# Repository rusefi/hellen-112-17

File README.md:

# hellen-112-17

[User Documentation](https://github.com/rusefi/rusefi/wiki/Hellen112-17)

[Interactive Pinout](https://rusefi.com/docs/pinouts/hellen/hellen-112-17/)

[Firmware Source Code](https://github.com/rusefi/rusefi/tree/master/firmware/config/boards/hellen/hellen-112-17)

# Compatibility

Bosch 21126-1411020-45

Bosch 21126-1411020-49

Bosch 21126-1411020-70

Suzuki 33910-69L01

Polaris Slingshot 4015316

Maybe 391F2-03FA0 HYUNDAI I20 1.2 16V?

Maybe 39124-2B500 KIA FORTE 1.6?

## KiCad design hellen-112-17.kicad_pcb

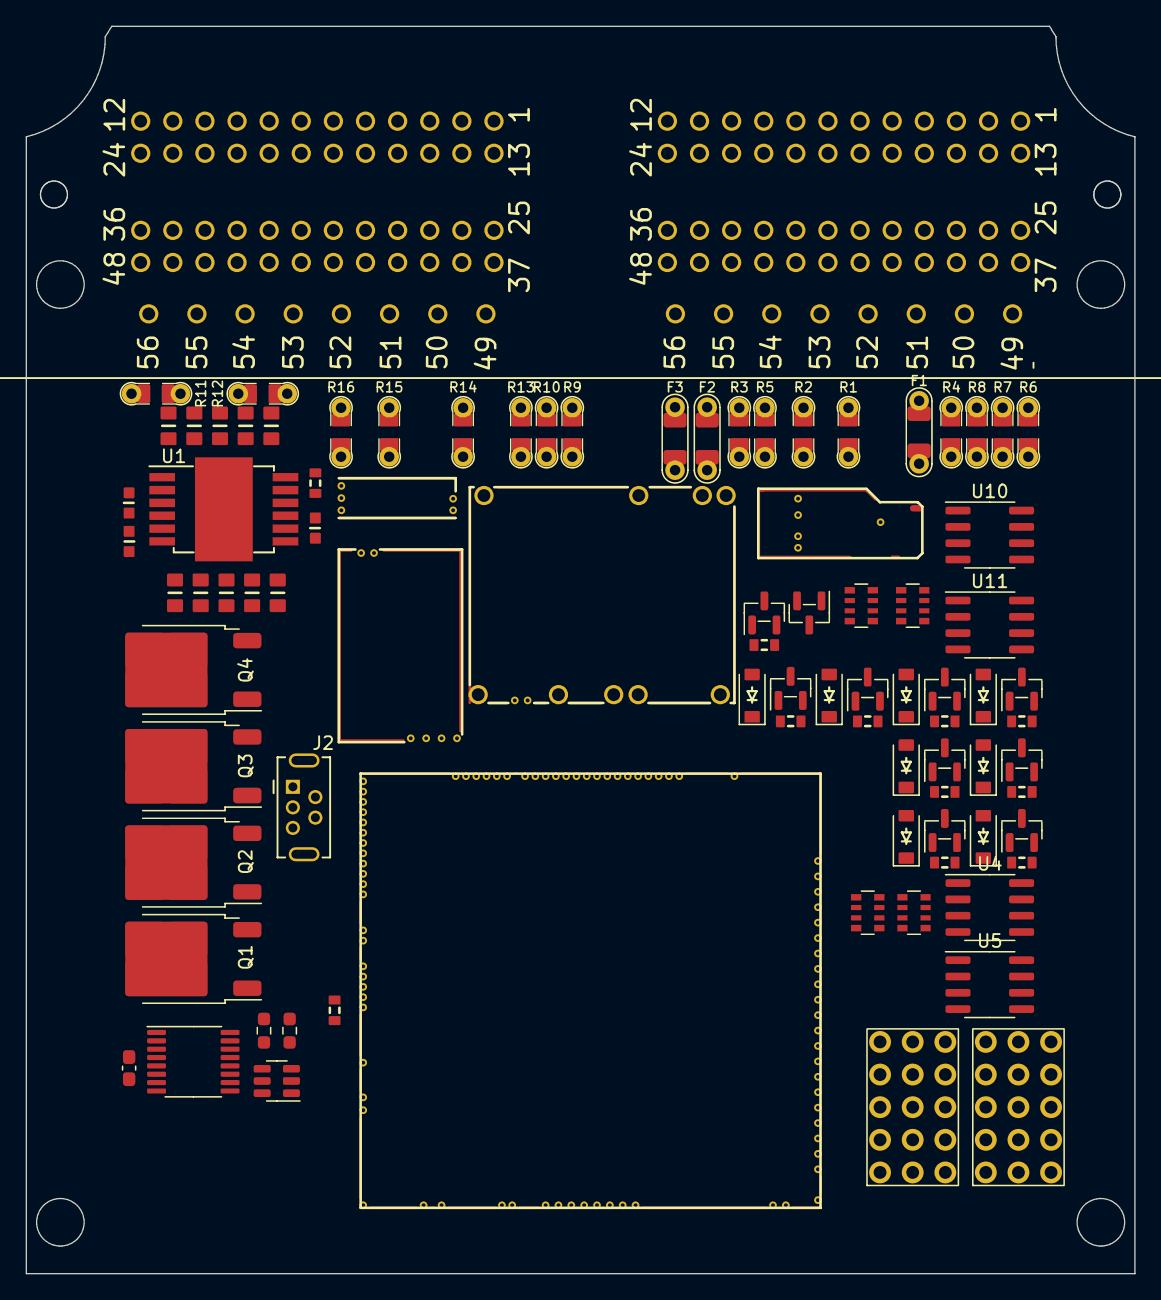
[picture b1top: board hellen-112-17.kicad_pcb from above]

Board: 2 copper layers, 86.3 x 97.1 mm, 88 parts (0 on the bottom side), 132 nets, no tracks yet.

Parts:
C1, C2, C3, C4, C5, C6, C7, C8, C9, C10: 10u; C0805
C11: 100n; C0603
C12, C13: 10n; C0603
C14: 100n; C_0603_1608Metric_Pad1.08x0.95mm_HandSolder
D1: PSM712-LF; SOT-23
D2, D3, D4, D5, D6, D7, D8, D9: B5819W; SOD-123
F1, F2, F3: 12H1500D; PAD-1206-PAD
G1, G2: PROTO_AREA
J1: rusefi_2x56_pin_conn; rusefi_2x56_pin_connector
J2: USB_B_Mini; USB-MINI-B-VERTICAL
M1: Module-power_12and5V-0.2; power_12and5V
M2: Module-vr-max9924-0.1; vr-max9924
M3: Module-knock-0.2; knock
M4: Module:mega_mcu100/0.1; mega-mcu100
M5: Module-lin-0.1; lin
Q1, Q2, Q3, Q4: ISL9V3040D3S; TO-252-2
Q5, Q6, Q7, Q8, Q9, Q10, Q11, Q12, Q13: AO3400A; SOT-23
R1, R2, R3, R4, R5, R6, R7, R8, R9, R10, R11, R12, R13, R14, R15, R16: Jumper-Pad-Pad; PAD-0805-PAD
R17, R18, R33, R34, R35, R36, R37, R38, R39, R40, R41: 4.7k; R0603
R19, R20: 4.7k; R_0603_1608Metric_Pad0.98x0.95mm_HandSolder
R44, R45, R46, R47: 1k; R_Array_Convex_4x0603
U1: TLE9201SG; Infineon_PG-DSO-12-11
U4, U5, U10, U11: VNLD5160; SOIC-8_3.9x4.9mm_P1.27mm
U6: SRV05-4; SOT-23-6
U7: 74VHC163FT; TSSOP-16_4.4x5mm_P0.65mm

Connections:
+3.3V: M4.N21 (V33), R18.2, U1.2 (VSO)
+3.3VA: G1.3, G1.8, G1.13, M4.N15 (V33_SWITCHABLE)
+5V: M1.E4 (V5), M4.N22 (VCC)
+5VA: C14.2, G1.4, G1.9, G1.14, M2.E4 (V5_IN), M3.E1 (V5A), M4.E1 (V5A_SWITCHABLE), M4.W2 (V5A_SWITCHABLE), M5.V3 (5V), R19.2, U6.5 (VP), U7.1 (~MR), U7.7 (CEP), U7.9 (~PE), U7.10 (CET), U7.16 (VCC)
+5VP: J1.37, J1.66, M1.V4 (5VP), R6.2, R7.2, R8.2, R11.2
+12V: M1.E2 (V12), M5.N1 (12V), M5.V1 (12V)
+12V_RAW: C1.2, C2.2, C3.2, C4.2, C5.2, C6.2, C7.2, C8.2, C9.2, C10.2, C11.2, D2.1 (K), D3.1 (K), D4.1 (K), D5.1 (K), D6.1 (K), D7.1 (K), D8.1 (K), D9.1 (K), F2.2, F3.2, G1.5, G1.10, G1.15, M1.V1 (V12_PERM), M1.V3 (V12_RAW), U1.4 (VS)
/CAN+: J1.32, M4.W11 (CANH)
/CAN-: J1.44, M4.W12 (CANL)
/CRANK_VR: M2.E3 (OUT), M4.S14 (IN_CRANK_(PB1))
/ETB_DIR: M4.E8 (SPI2_MISO_(PB14)), U1.1 (DIR)
/ETB_DIS: M4.E9 (SPI2_MOSI_(PB15)), R18.1, U1.11 (DIS)
/ETB_PWM: M4.E23 (OUT_PWM6_(PD14)), U1.12 (PWM)
/IGN1: M4.W10 (IGN1_(PC13)), Q1.1 (G)
/IGN2: M4.W9 (IGN2_(PE5)), Q2.1 (G)
/IGN3: M4.W8 (IGN3_(PE4)), Q3.1 (G)
/IGN4: M4.W7 (IGN4_(PE3)), Q4.1 (G)
/INJ1: M4.E17 (OUT_INJ1_(PD3)), R44.8 (R1.2), R45.5 (R4.2)
/INJ2: M4.E16 (OUT_INJ2_(PA9)), R44.6 (R3.2), R45.7 (R2.2)
/INJ3: M4.E15 (OUT_INJ3_(PD11)), R44.7 (R2.2), R45.6 (R3.2)
/INJ4: M4.E14 (OUT_INJ4_(PD10)), R44.5 (R4.2), R45.8 (R1.2)
/IN_AV_107: M4.S16 (IN_CAM_(PA6)), R1.2
/IN_AV_109: J1.9, M4.S12 (IN_MAP2_(PC1))
/IN_AV_110: J1.10, M4.S9 (IN_AUX1_(PB0))
/IN_AV_111: M4.S8 (IN_AUX2_(PC4/PE9)), R3.2
/IN_AV_112: J1.12, M4.S7 (IN_AUX3_(PC5))
/IN_AV_119: J1.19, M4.S6 (IN_AUX4_(PA7))
/IN_CAM: J1.87, M4.S4 (IN_D1_(PE12))
/IN_CLT: J1.71, M4.S21 (IN_CLT_(PC2))
/IN_CRANK_VR+: M2.W2 (VR+), R10.2
/IN_CRANK_VR-: M2.W1 (VR-), R9.2
/IN_DIGITAL_113: J1.13, M4.S2 (IN_D3_(PE14))
/IN_DIGITAL_120: J1.20, M4.S1 (IN_D4_(PE15))
/IN_DIGITAL_123: J1.23, M4.E7 (SPI2_SCK_/_CAN2_TX_(PB13))
/IN_DIGITAL_134_HS: J1.34, M4.N10 (SPI3_SCK_(PC10))
/IN_DIGITAL_135_HS: J1.35, M4.N11 (SPI3_MISO_(PC11))
/IN_DIGITAL_136_HS: J1.36, M4.N9 (SPI3_CS_(PA15))
/IN_DIGITAL_147_HS: J1.47, M4.E6 (SPI2_CS_/_CAN2_RX_(PB12))
/IN_IAT: J1.83, M4.S20 (IN_IAT_(PC3))
/IN_KNOCK: M3.E3 (OUT_KNOCK), M4.S15 (IN_KNOCK_(PA2))
/IN_KNOCK_RAW: M3.W1 (IN_KNOCK), R13.2
/IN_MAF_DIGITAL: R12.2, R19.1, R20.2
/IN_MAP: J1.75, M4.S13 (IN_MAP1_(PC0))
/IN_PPS1: M4.S19 (IN_PPS_(PA3)), R5.2
/IN_PPS2: M4.S10 (IN_O2S2_(PA1)), R4.2
/IN_TPS1: J1.59, M4.S18 (IN_TPS_(PA4))
/IN_TPS2: J1.76, M4.S11 (IN_O2S_/_CAN_WAKEUP_(PA0))
/IN_VIGN: F1.2, M1.V2 (IN_VIGN)
/IN_VSS: J1.88, M4.S3 (IN_D2_(PE13))
/K-Line: J1.27, M5.V4 (LIN)
/MAF_DIGITAL: M4.S17 (IN_VSS_(PE11)), U7.12 (Q2)
/OUT_AC: D7.2 (A), J1.31, Q11.2 (D)
/OUT_ETB+: C13.2, R15.2, U1.7 (OUT2)
/OUT_ETB-: C12.2, R16.2, U1.5 (OUT1)
/OUT_FAN_RELAY: D8.2 (A), J1.41, Q12.2 (D)
/OUT_FUEL: D6.2 (A), J1.29, Q10.2 (D)
/OUT_FUEL_PUMP_RELAY: D9.2 (A), J1.42, Q13.2 (D)
/OUT_IGN1: J1.112, Q1.2 (C)
/OUT_IGN2: J1.109, Q2.2 (C)
/OUT_IGN3: J1.110, Q3.2 (C)
/OUT_IGN4: J1.111, Q4.2 (C)
/OUT_INJ1: J1.100, U4.8 (D1)
/OUT_INJ2: J1.98, U4.6 (D2)
/OUT_INJ3: J1.99, U5.8 (D1)
/OUT_INJ4: J1.101, U5.6 (D2)
/OUT_LS_101: J1.1, U10.8 (D1)
/OUT_LS_102: J1.2, U10.6 (D2)
/OUT_LS_235: J1.91, U11.8 (D1)
/OUT_LS_246: J1.102, U11.6 (D2)
/OUT_MAIN_RELAY: D1.1, J1.15, Q8.2 (D)
/OUT_RELAY_140: D4.2 (A), J1.40, Q7.2 (D)
/OUT_RELAY_151: D2.2 (A), J1.51, Q5.2 (D)
/OUT_RELAY_152: D3.2 (A), J1.52, Q6.2 (D)
/OUT_TACH: D5.2 (A), J1.28, Q9.2 (D)
/PWR_EN: M1.E5 (EN_5VP), M4.N20 (OUT_PWR_EN_(PE10))
/TLS115_PG: M1.E6 (PG_5VP), M4.N12 (SPI3_MOSI_(PC12))
/USB+: J2.3 (D+), M4.N3 (USBP_(PA12))
/USB-: J2.2 (D-), M4.N2 (USBM_(PA11))
/VBAT: M1.E1 (VBAT), M4.N17 (VBAT)
/VBUS: J2.1 (VBUS), M4.N1 (VBUS)
/VIGN: M1.E3 (VIGN), M4.E5 (IN_VIGN_(PA5))
/VREF2: M3.W2 (VREF), M4.S5 (VREF2)
/lowside_quad1/IN1: M4.E13 (OUT_INJ5_(PD2)), R46.8 (R1.2), R47.5 (R4.2)
/lowside_quad1/IN2: M4.E11 (OUT_INJ7_(PD15)), R46.7 (R2.2), R47.6 (R3.2)
/lowside_quad1/IN3: M4.E12 (OUT_INJ6_(PA8)), R46.6 (R3.2), R47.7 (R2.2)
/lowside_quad1/IN4: M4.E10 (OUT_INJ8_(PD12)), R46.5 (R4.2), R47.8 (R1.2)
/lowside_weak/IN1: M4.W6 (IGN5_(PE2)), Q5.1 (G), R33.1
/lowside_weak/IN2: M4.W5 (IGN6_(PB8)), Q6.1 (G), R34.1
/lowside_weak/IN3: M4.W4 (IGN7_(PB9)), Q7.1 (G), R35.1
/lowside_weak/IN4: M4.W3 (IGN8_(PE6)), Q8.1 (G), R36.1
/lowside_weak/IN5: M4.E18 (OUT_PWM1_(PD13)), Q9.1 (G), R37.1
/lowside_weak/IN6: M4.E19 (OUT_PWM2_(PC6)), Q10.1 (G), R38.1
/lowside_weak/IN7: M4.E20 (OUT_PWM3_(PC7)), Q11.1 (G), R39.1
/lowside_weak/IN8: M4.E21 (OUT_PWM4_(PC8)), Q12.1 (G), R40.1
/lowside_weak/IN9: M4.E22 (OUT_PWM5_(PC9)), Q13.1 (G), R41.1
GND: C1.1, C2.1, C3.1, C4.1, C5.1, C6.1, C7.1, C8.1, C9.1, C10.1, C11.1, C12.1, C13.1, C14.1, D1.2, G1.1, G1.2, G1.6, G1.7, G1.11, G1.12, J1.53, J1.54, J1.106, J2.5 (GND), J2.6 (Shield), M1.S1 (GND), M2.G (GND), M3.E2 (GND), M4.G (GND), M5.E1 (GND), M5.S1 (GND), Q1.3 (E), Q2.3 (E), Q3.3 (E), Q4.3 (E), Q5.3 (S), Q6.3 (S), Q7.3 (S), Q8.3 (S), Q9.3 (S), Q10.3 (S), Q11.3 (S), Q12.3 (S), Q13.3 (S), R2.2, R33.2, R34.2, R35.2, R36.2, R37.2, R38.2, R39.2, R40.2, R41.2, R44.1 (R1.1), R44.2 (R2.1), R44.3 (R3.1), R44.4 (R4.1), R46.1 (R1.1), R46.2 (R2.1), R46.3 (R3.1), R46.4 (R4.1), U1.6 (GND), U1.8 (SI), U1.9 (CSN), U1.10 (SCK), U1.13 (GND), U4.5 (S2), U4.7 (S1), U5.5 (S2), U5.7 (S1), U6.2 (VN), U7.3 (D0), U7.4 (D1), U7.5 (D2), U7.6 (D3), U7.8 (GND), U10.5 (S2), U10.7 (S1), U11.5 (S2), U11.7 (S1)
GNDA: J1.3, J1.4, J1.5, J1.6, J1.60, J1.61, J1.62, J1.63, J1.64, J1.103, M4.W1 (GNDA), R14.2
unnamed: F1.1, J1.16
unnamed: F2.1, J1.55
unnamed: F3.1, J1.56
unnamed: G2.1, G2.6, G2.11
unnamed: G2.5, G2.10, G2.15
unnamed: G2.2, G2.7, G2.12
unnamed: G2.3, G2.8, G2.13
unnamed: G2.4, G2.9, G2.14
unnamed: J1.7, R1.1
unnamed: J1.8, R2.1
unnamed: J1.11, R3.1
unnamed: J1.14, R4.1
unnamed: J1.21, R5.1
unnamed: J1.25, R6.1
unnamed: J1.26, R7.1
unnamed: J1.38, R8.1
unnamed: J1.57, R9.1
unnamed: J1.69, R10.1
unnamed: J1.79, R11.1
unnamed: J1.89, R12.1
unnamed: J1.93, R13.1
unnamed: J1.94, R14.1
unnamed: J1.107, R15.1
unnamed: J1.108, R16.1
unnamed: M4.N18 (UART8_RX_(PE0)), M5.V2 (UART_RX), R17.2
unnamed: M4.N19 (UART8_TX_(PE1)), M5.V5 (UART_TX)
unnamed: R45.1 (R1.1), U5.3 (IN2)
unnamed: R45.2 (R2.1), U5.1 (IN1)
unnamed: R45.3 (R3.1), U4.3 (IN2)
unnamed: R45.4 (R4.1), U4.1 (IN1)
unnamed: R47.1 (R1.1), U11.3 (IN2)
unnamed: R47.2 (R2.1), U11.1 (IN1)
unnamed: R47.3 (R3.1), U10.3 (IN2)
unnamed: R47.4 (R4.1), U10.1 (IN1)
unnamed: R20.1, U6.1 (IO1), U6.3 (IO2), U6.4 (IO3), U6.6 (IO4), U7.2 (CP)

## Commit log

2022-11-18 hello
2022-11-19 Init project
2022-11-19 Lib remove
2023-09-04 progress
2023-09-04 fresh
2023-09-05 #3 #4 #5 #6
2023-09-05 пронумеровала, перенесла изменения на плату
2023-09-08 automation
2023-09-09 Upd SCH
2023-09-10 revision
2023-09-10 [skip actions] Auto-generated board
2023-09-10 Export
2023-09-10 Update hellen-one
2023-09-10 Update mm100, connector, replace
2023-09-10 srv05 value fix
2023-09-10 Warnings fix
2023-09-10 #18, #19
2023-09-10 # STM32F407VGT6 is very cheap U105,"STM32F429VGT6","LQFP100","C12345"
2023-09-11 fab A
2023-09-30 112-17-b
2023-09-30 112-17-b copy of a
2023-10-01 MM100_0.2
2023-12-01 just a test
2024-01-13 reusing rusefi/rusefi/.github/workflows/gen-pinouts-top-level.yaml@master
2024-08-09 Marsel has ordered rev B
2024-11-30 actions
2024-11-30 GHA says update hellen-one
2024-11-30 [skip actions] Auto-generated board v2.1
